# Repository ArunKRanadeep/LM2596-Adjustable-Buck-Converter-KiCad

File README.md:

# LM2596-Adjustable-Buck-Converter-KiCad
DC-DC Adjustable Buck Converter PCB design using LM2596-ADJ created in KiCad.

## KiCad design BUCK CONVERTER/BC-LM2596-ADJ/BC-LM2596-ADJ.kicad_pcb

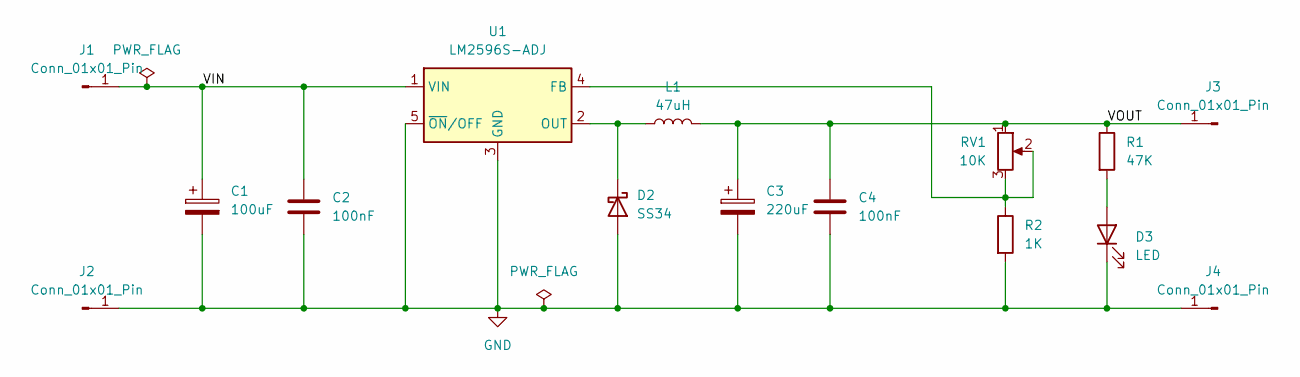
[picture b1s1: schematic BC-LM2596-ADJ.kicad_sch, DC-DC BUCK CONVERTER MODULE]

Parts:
C1: 100uF; C_Elec_8x10.2
C2, C4: 100nF; C_0603_1608Metric
C3: 220uF; C_Elec_8x10.2
D2: SS34; D_SMA
D3: LED; LED_0603_1608Metric
J1, J2, J3, J4: Conn_01x01_Pin; PinHeader_1x01_P2.54mm_Vertical
L1: 47uH; L_Bourns_SRR1208_12.7x12.7mm
R1: 47K; R_0603_1608Metric
R2: 1K; R_0603_1608Metric
RV1: 10K; Potentiometer_Bourns_3296W_Vertical
U1: LM2596S-ADJ; TO-263-5_TabPin3

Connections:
/VIN: C1.1, C2.1, J1.1, U1.1 (VIN)
/VOUT: C3.1, C4.1, J3.1, L1.2, R1.1, RV1.1
GND: C1.2, C2.2, C3.2, C4.2, D2.2 (A), D3.1 (K), J2.1, J4.1, R2.2, U1.3 (GND), U1.5 (~ON/OFF); also elsewhere on the board
unnamed: D2.1 (K), L1.1, U1.2 (OUT)
unnamed: D3.2 (A), R1.2
unnamed: R2.1, RV1.2, RV1.3, U1.4 (FB)

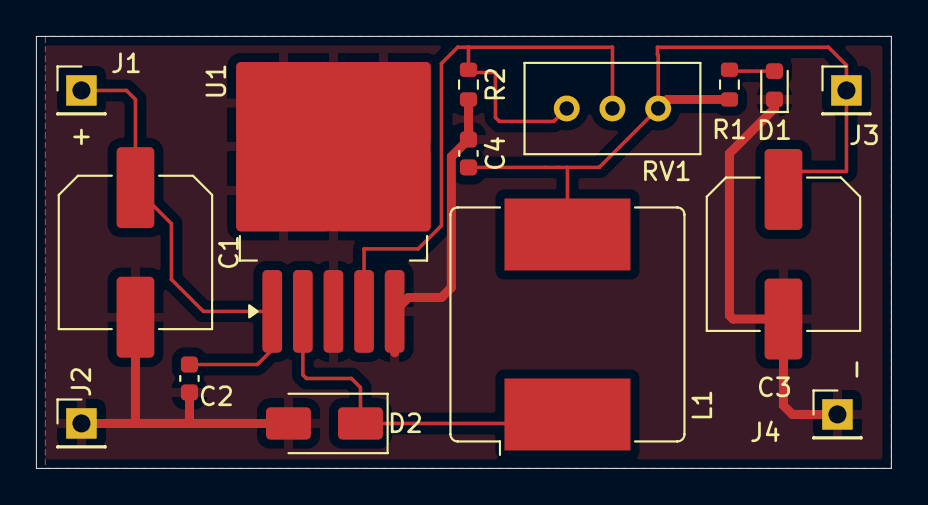
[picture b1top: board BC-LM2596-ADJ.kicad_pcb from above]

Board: 2 copper layers, 47.5 x 24.0 mm, 15 parts (0 on the bottom side), 5 nets.

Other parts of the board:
D1: LED; LED_0603_1608Metric

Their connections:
GND: D1.1 (K); also elsewhere on the board

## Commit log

2026-03-11 Initial commit - LM2596 Buck Converter PCB Design
    # LM2596 Adjustable Buck Converter (KiCad)
    This project is a DC-DC Adjustable Buck Converter PCB designed using KiCad.
    ## Features
    - LM2596-ADJ step-down regulator
    - Adjustable output voltage
    - Multi-turn potentiometer for precise control
2026-03-11 Rename zero error.png to ERROR CHECK.png
2026-03-11 Rename ERROR CHECK.png to ERC CHECK.png
2026-03-11 Rename ERC CHECK.png to ERC.png
2026-03-11 Rename zero error1.png to IMG.png
2026-03-11 Rename PCB.png to 3D VIEW 1.png
2026-03-11 Rename 3D VIEW.png to 3D VIEW 2.png
